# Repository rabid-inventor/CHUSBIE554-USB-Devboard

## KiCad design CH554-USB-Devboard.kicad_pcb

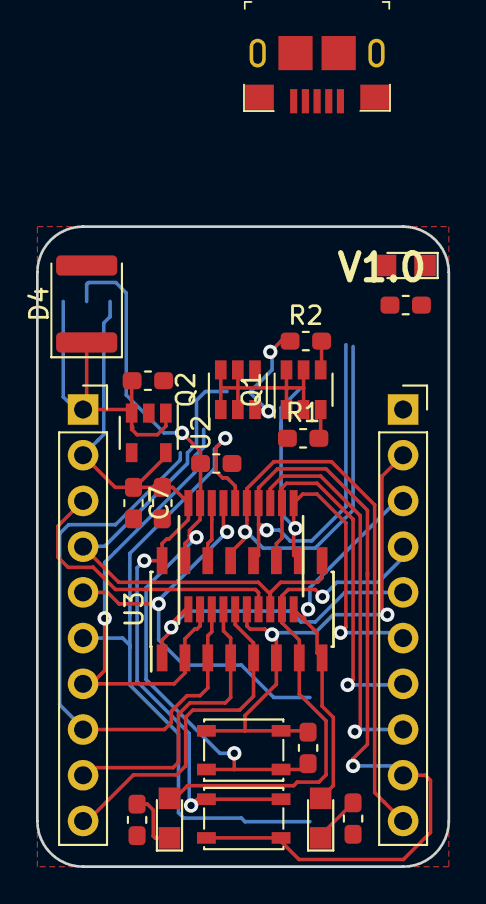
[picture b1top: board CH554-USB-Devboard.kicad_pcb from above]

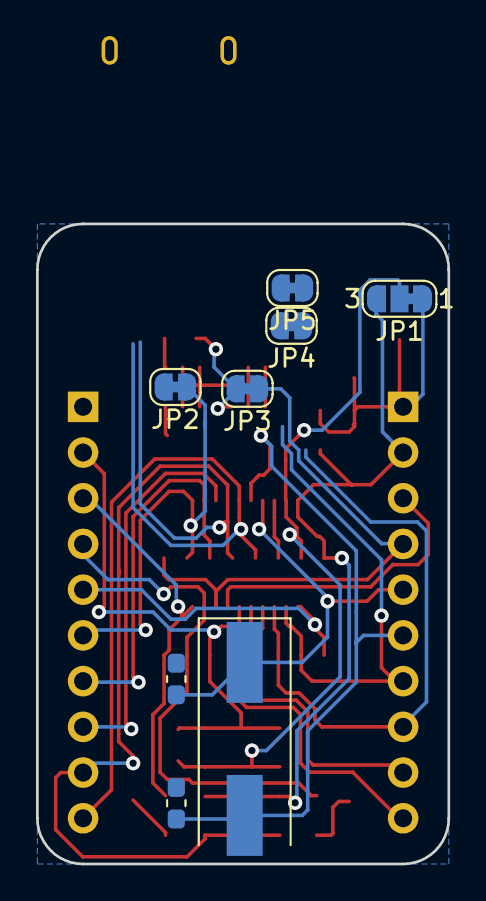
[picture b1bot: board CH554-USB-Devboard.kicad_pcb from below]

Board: 2 copper layers, 22.9 x 35.6 mm, 32 parts (8 on the bottom side), 28 nets.

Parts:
C1, C2, C4, C7: 100nF; C_0603_1608Metric_Pad1.05x0.95mm_HandSolder
C3: 100uF; C_0603_1608Metric_Pad1.05x0.95mm_HandSolder
C5, C6: 15pF; C_0603_1608Metric_Pad1.05x0.95mm_HandSolder
D1, D2, D3: LED; LED_0805
D4: SMBJ58A+; D_1812_4532Metric
J1, J2: Conn_01x10_Male; PinSocket_1x10_P2.54mm_Vertical
J3: USB_C_Receptacle; USB_Micro_B_Female_10118193-0001LF
JP1: Jumper_3_Bridged12; SolderJumper-3_P1.3mm_Bridged12_RoundedPad1.0x1.5mm_NumberL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
JP2, JP3, JP4, JP5: Jumper_NC_Small; SolderJumper-2_P1.3mm_Bridged_RoundedPad1.0x1.5mm
Q1, Q2: CPH6337; SOT-23-6
R1, R2: 10k; R_0603_1608Metric_Pad1.05x0.95mm_HandSolder
R3, R4: 330r; R_0603_1608Metric_Pad1.05x0.95mm_HandSolder
R5: 300r; R_0603_1608Metric_Pad1.05x0.95mm_HandSolder
SW1, SW2: SW_Push; SW_SPST_PTS810
U1: CH554T; TSSOP-20_4.4x6.5mm_Pitch0.65mm
U2: MIC5504-3.3YM5; SOT-23-5
U3: CH554G; SOIC-16_3.9x9.9mm_Pitch1.27mm
Y1: Crystal; Crystal_SMD_HC49-SD

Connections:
+3V3: C2.1, C7.1, J1.2, JP1.3, SW1.1, U1.20, U2.5, U3.16
/P1.0: J1.3, U1.7
/P1.1: J1.4, JP3.1, U1.8, U3.9
/P1.2: C5.1, J1.5, U1.17, Y1.1
/P1.3: C6.1, J1.6, U1.16, Y1.2
/P1.4: J1.7, JP4.2, U1.2, U3.2
/P1.5: J1.8, JP5.2, U1.3, U3.3
/P1.6: J1.9, U1.4, U3.4
/P1.7: J1.10, U1.5, U3.5
/P3.0: D2.2, J2.3, U1.10, U3.8
/P3.1: D1.2, J2.4, U1.9, U3.7
/P3.2: J2.5, U1.1, U3.1
/P3.3: J2.6, JP2.1, U1.11, U3.10
/P3.4: J2.7, U1.12, U3.11
/P3.5: J2.8, U1.13
/P3.6: J2.9, SW1.2, U1.14, U3.12
/P3.7: J2.10, U1.15, U3.13
/RESET: C3.2, J2.2, SW2.1, U1.6, U3.6
/VSYS: C1.1, C3.1, JP1.2, SW2.2, U1.19, U3.15
GND: C1.2, C2.2, C4.2, C5.2, C6.2, C7.2, D3.1, D4.2, J2.1, R1.1, R3.1, R4.1, U1.18, U2.2, U3.14
unnamed: D1.1, R3.2
unnamed: D2.1, R4.2
unnamed: D3.2, R5.2
unnamed: JP2.2, Q1.3, R1.2
unnamed: JP3.2, Q2.3, R2.1
unnamed: Q1.1, Q1.2, Q1.5, Q1.6, Q2.1, Q2.2, Q2.5, Q2.6
VBUS: Q1.4, R2.2
VCC: C4.1, D4.1, J1.1, JP1.1, Q2.4, R5.1, U2.1, U2.3

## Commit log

2020-06-16 first commit used CHUSBIE552 as base
2020-06-16 relinked libs
2020-06-16 needs VBUS to VCC control
2020-06-17 schematic complete started to route
2020-06-18 more routing
